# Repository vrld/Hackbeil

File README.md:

# Hackbeil (/ˈhakˌbaɪ̯l/)

My custom 60 key wireless split keyboard. Inspired by [Lily58](https://github.com/kata0510/Lily58). (Will be) Built with [ergogen](https://ergogen.xyz) and [zmk](https://zmk.dev).

## Setup

Install ergogen, e.g., with `yarn`:

    yarn global add ergogen

## Building

Using `make`:

    make

The output will be placed in the `build` directory.

Next, use KiCad to add traces or try your luck with freerouting.
That will likely require some modifications to the footprints though.

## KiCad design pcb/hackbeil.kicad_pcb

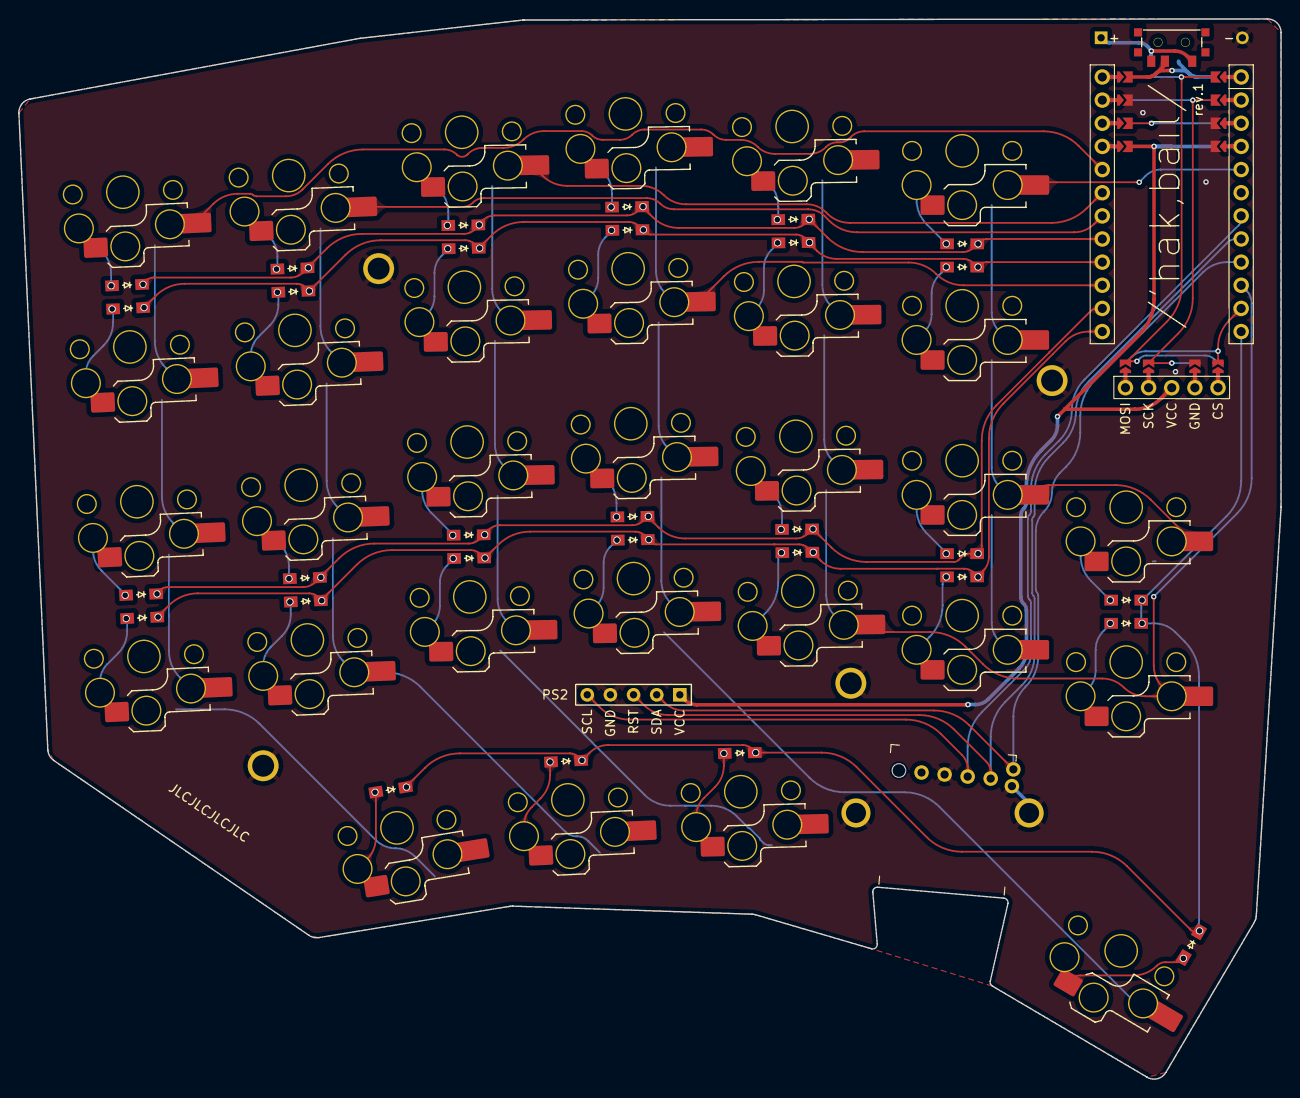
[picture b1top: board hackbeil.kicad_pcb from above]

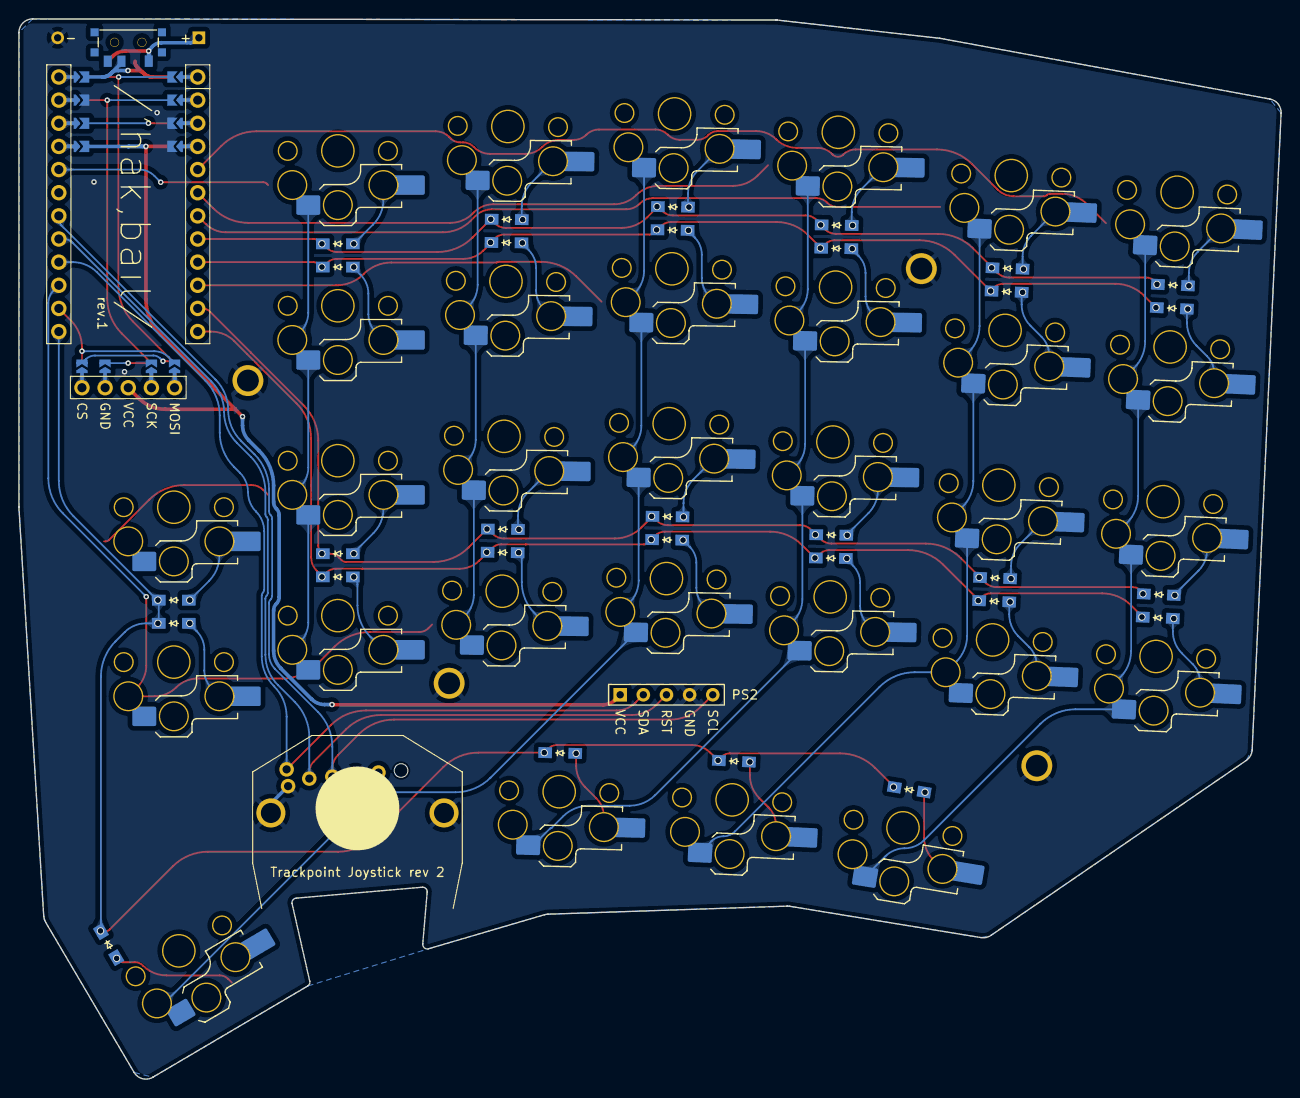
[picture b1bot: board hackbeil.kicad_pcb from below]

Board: 2 copper layers, 138.5 x 116.3 mm, 71 parts (31 on the bottom side), 55 nets.

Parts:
BAT1: battery
D1, D2, D3, D4, D5, D6, D7, D8, D9, D10, D11, D12, D13, D14, D15, D16, D17, D18, D19, D20, D21, D22, D23, D24, D25, D26, D27, D28, D29, D30: diode
DISP1: nice_view
MCU1: mcu_nice_nano
MH1, MH2, MH3, MH4: mounting_hole
RotaryEncoder_EVQWGD0011: RollerEncoder_EVQWGD001; RotaryEncoder_EVQWGD001
S1, S2, S3, S4, S5, S6, S7, S8, S9, S10, S11, S12, S13, S14, S15, S16, S17, S18, S19, S20, S21, S22, S23, S24, S25, S26, S27, S28, S29, S30: switch_choc_v1_v2
T1: SPDT_C128955
TPH1: trackpoint_header
TPJ1: trackpad_joystick_mounting_holes

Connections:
COL0: MCU1.20, S1.1, S2.1, S3.1, S4.1, S27.1
COL1: MCU1.18, S5.1, S6.1, S7.1, S8.1, S28.1
COL2: MCU1.19, S9.1, S10.1, S11.1, S12.1, S29.1
COL3: MCU1.15, S13.1, S14.1, S15.1, S16.1, S30.1
COL4: MCU1.10, S17.1, S18.1, S19.1, S20.1, S25.1
COL5: MCU1.5, S21.1, S22.1, S23.1, S24.1, S26.1
DISP1_0: DISP1.0, DISP1.5, DISP1.15
DISP1_1: DISP1.1, DISP1.6, DISP1.16
DISP1_3: DISP1.3, DISP1.8, DISP1.18
DISP1_4: DISP1.4, DISP1.9, DISP1.19
GND: BAT1.2, DISP1.13, DISP1.21, MCU1.103, MCU1.104, MCU1.123, RotaryEncoder_EVQWGD0011.C, RotaryEncoder_EVQWGD0011.S2, TPH1.4
NV_CS: DISP1.14, DISP1.20, MCU1.11
NV_MOSI: DISP1.10, DISP1.24, MCU1.101
NV_SCK: DISP1.11, DISP1.23, MCU1.102
RAW: MCU1.124, T1.2
ROW0: D2.1, D2.3, D4.1, D4.3, D6.1, D6.3, D8.1, D8.3, D10.1, D10.3, D12.1, D12.3, MCU1.17
ROW1: D15.1, D15.3, D17.1, D17.3, D19.1, D19.3, D21.1, D21.3, D23.1, D23.3, D25.1, D25.3, MCU1.16
ROW2: D1.1, D1.3, D3.1, D3.3, D5.1, D5.3, D7.1, D7.3, D9.1, D9.3, D11.1, D11.3, MCU1.14
ROW3: D14.1, D14.3, D16.1, D16.3, D18.1, D18.3, D20.1, D20.3, D22.1, D22.3, D24.1, D24.3, MCU1.13
ROW4: D13.1, D13.3, D26.1, D26.3, D27.1, D27.3, D28.1, D28.3, D29.1, D29.3, D30.1, D30.3, MCU1.12
TP_RST: MCU1.8, RotaryEncoder_EVQWGD0011.A, TPH1.3
TP_SCL: MCU1.7, RotaryEncoder_EVQWGD0011.B, TPH1.5
TP_SDA: MCU1.9, RotaryEncoder_EVQWGD0011.S1, TPH1.2
VCC: DISP1.2, MCU1.121, TPH1.1
index_bottom: D22.2, D22.4, S17.2
index_home: D9.2, D9.4, S18.2
index_mod: D29.2, D29.4, S29.2
index_number: D10.2, D10.4, S20.2
index_top: D23.2, D23.4, S19.2
inner_bottom: D24.2, D24.4, S21.2
inner_home: D11.2, D11.4, S22.2
inner_number: D12.2, D12.4, S24.2
inner_top: D25.2, D25.4, S23.2
innest_bottom: D26.2, D26.4, S25.2
innest_home: D13.2, D13.4, S26.2
innest_mod: D30.2, D30.4, S30.2
middle_bottom: D20.2, D20.4, S13.2
middle_home: D7.2, D7.4, S14.2
middle_mod: D28.2, D28.4, S28.2
middle_number: D8.2, D8.4, S16.2
middle_top: D21.2, D21.4, S15.2
outer_bottom: D14.2, D14.4, S1.2
outer_home: D1.2, D1.4, S2.2
outer_number: D2.2, D2.4, S4.2
outer_top: D15.2, D15.4, S3.2
pinky_bottom: D16.2, D16.4, S5.2
pinky_home: D3.2, D3.4, S6.2
pinky_number: D4.2, D4.4, S8.2
pinky_top: D17.2, D17.4, S7.2
ring_bottom: D18.2, D18.4, S9.2
ring_home: D5.2, D5.4, S10.2
ring_mod: D27.2, D27.4, S27.2
ring_number: D6.2, D6.4, S12.2
ring_top: D19.2, D19.4, S11.2
switch_from: BAT1.1, T1.1

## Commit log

2024-06-13 Key matrix and outlines; project boilerplate
2024-06-13 Add preview image
2024-06-14 Add PCB, tweak layout
2024-06-14 Remove unused file
2024-06-16 SMD diode only
2024-06-16 remove unused features from footprint
2024-06-16 Add trackpoint header footprint
2024-06-16 Move diodes to more convenient positions
2024-06-16 Flip pin order for rows and columns
    This makes routing easier
2024-06-16 Tweak nice!view header, trackpoint header, order number
2024-06-16 PCB pre-routing
2024-06-17 Fix wiring
2024-06-17 Refactor trackpoint header
2024-06-17 Refactor OLED header footprint
2024-06-20 Tweak footprints
2024-06-20 Tweak board layout
2024-06-20 Prepare for wiring
2024-06-20 Hand routed PCB
2024-06-20 Add teardrops and smooth traces
2024-06-22 Layout tweaks
2024-06-22 Add EVQWGD001 encoder, try freerouting
2024-06-22 Traced by combination of freerouting and manual routing
2024-06-22 Add teardrops
2024-06-22 Fancy rounded tracks (thanks, Mitxela!)
2024-06-23 Add keyplate, prepare 3d printed case
2024-06-25 Final routing and top plates
2024-07-05 Refactoring, dimensions
2024-07-07 Move ergogen config to sub dir
2024-07-07 Add case
2024-07-07 fix typo
